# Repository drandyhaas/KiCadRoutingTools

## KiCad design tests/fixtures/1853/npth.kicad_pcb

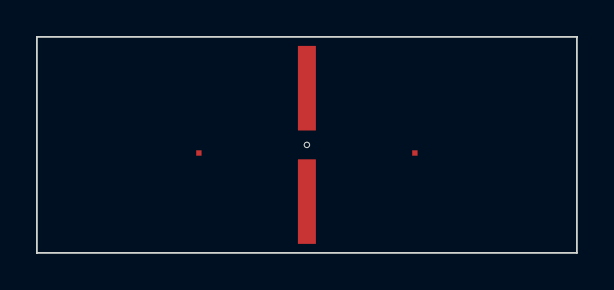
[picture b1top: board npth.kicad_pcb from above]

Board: 4 copper layers, 30.0 x 12.0 mm, 3 parts (0 on the bottom side), 2 nets, no tracks yet.

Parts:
H1: H1
P1: P1
W1: W1

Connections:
SIG: P1.1, P1.2
WALL: W1.1, W1.2

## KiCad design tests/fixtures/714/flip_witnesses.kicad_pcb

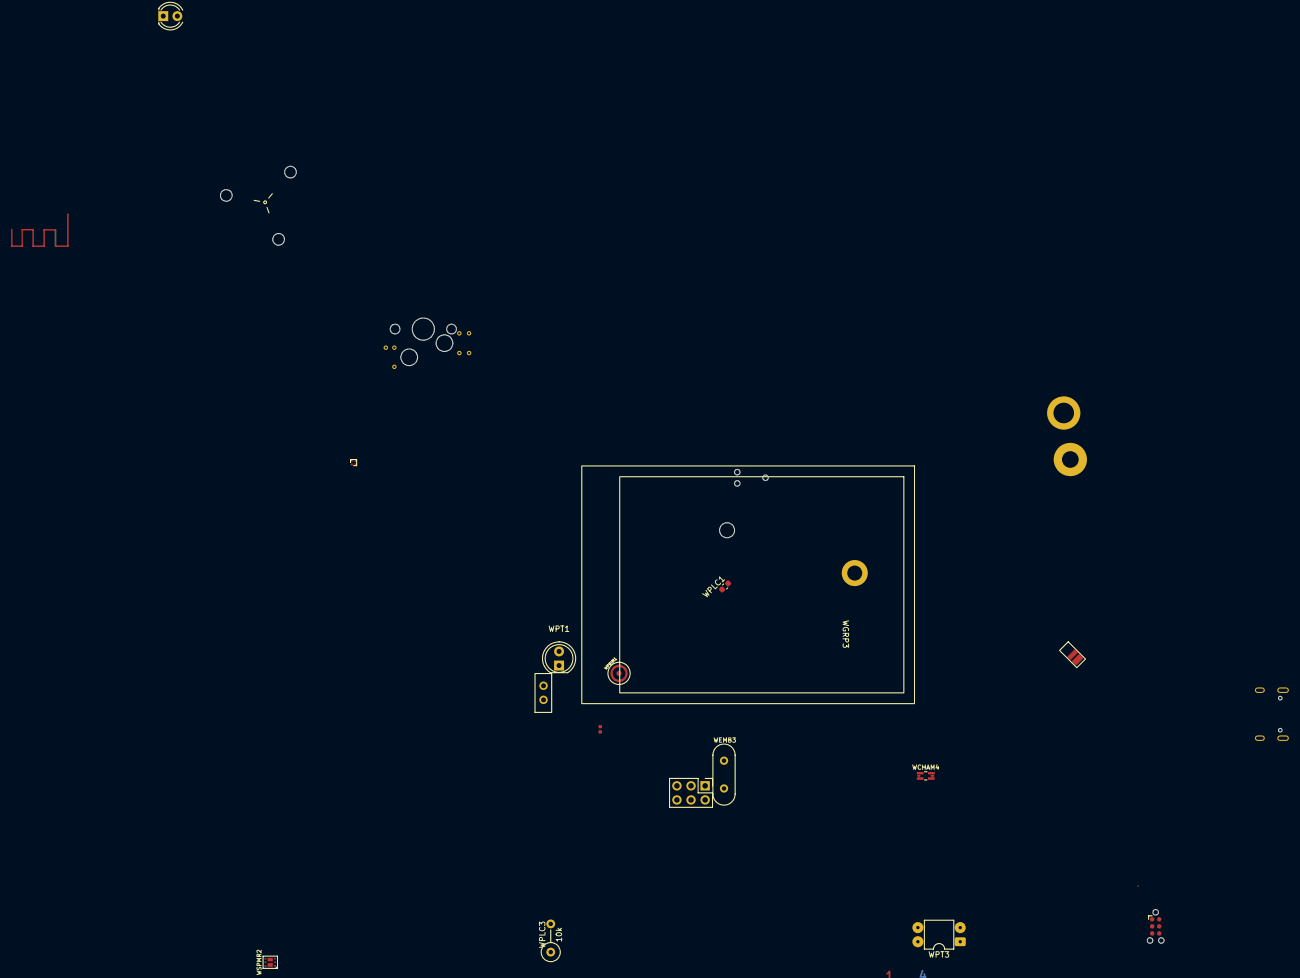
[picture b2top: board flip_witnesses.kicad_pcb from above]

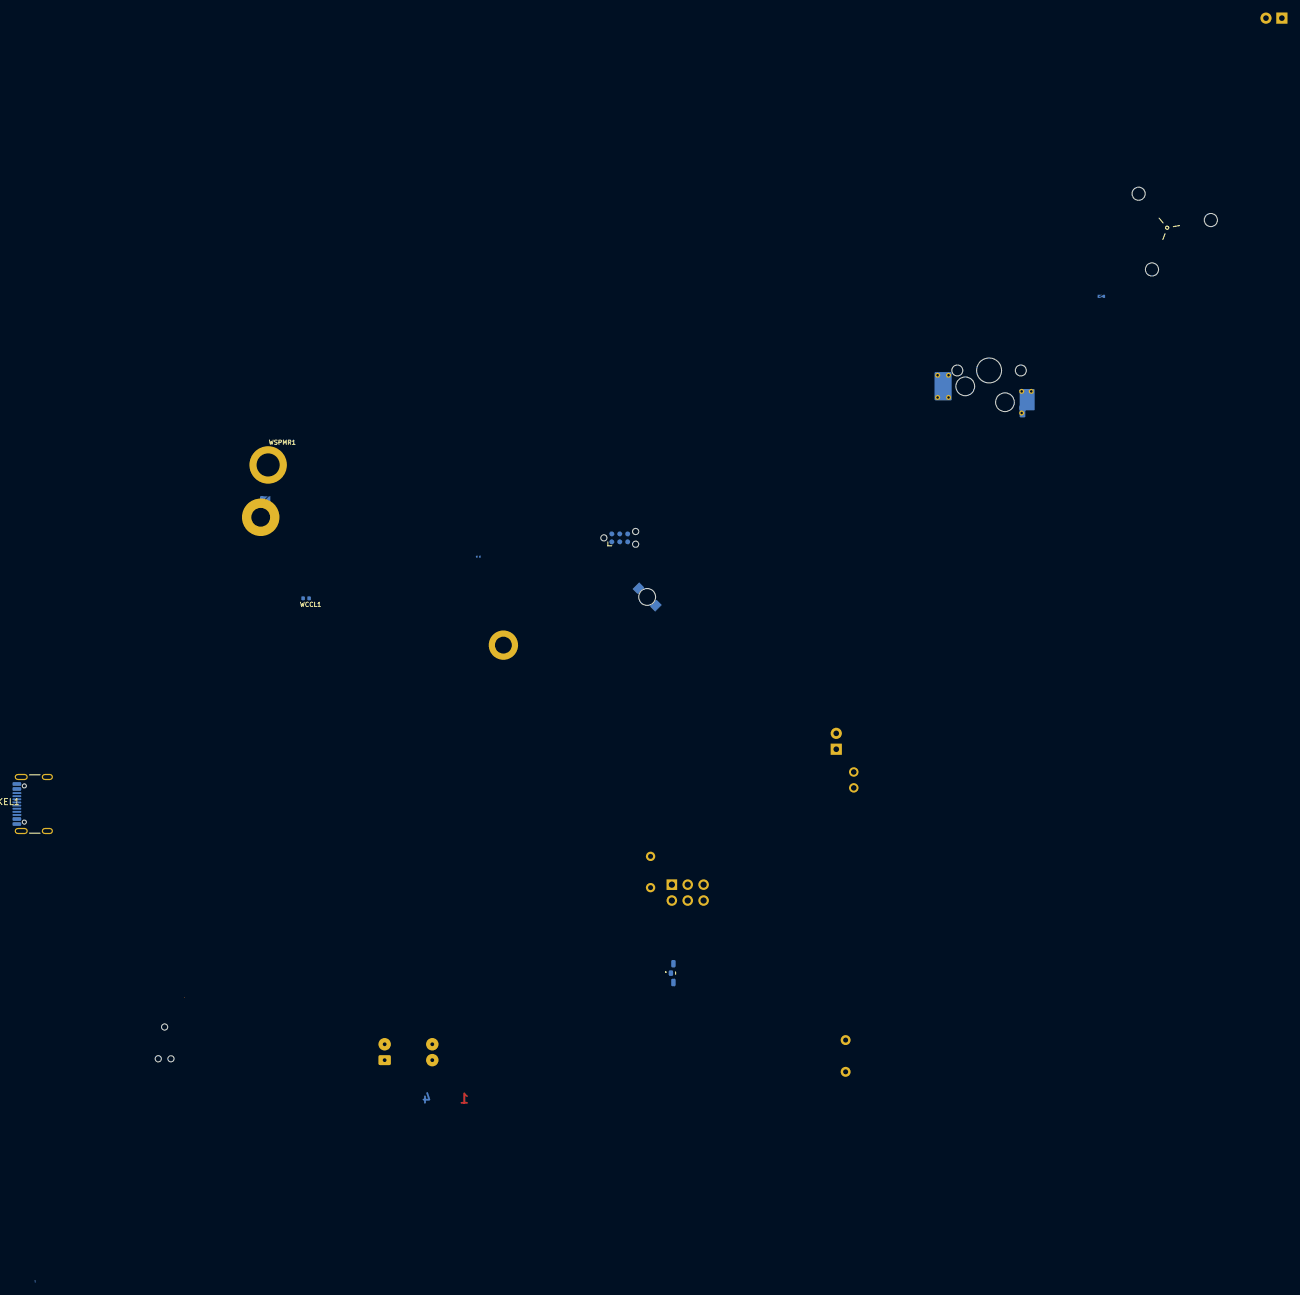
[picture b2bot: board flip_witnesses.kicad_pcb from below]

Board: 6 copper layers, 33 parts (11 on the bottom side), 6 nets, no tracks yet.

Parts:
WCCL1: R_49k9_0402; R_0402_1005Metric
WCCL2: R_0R01_330mW_0402; R_0402_1005Metric
WCHAM1: Net-Tie_2; NetTie-2_SMD_Pad0.127mm
WCHAM2: 100nF; C_0201
WCHAM3: Net-Tie_P0.127mm; NetTie-2_SMD_Pad0.127mm
WCHAM4: 5m; R_0805_2012Metric_4Kelvin
WEMB1: 2286211-3; TE_2286211-3
WEMB2: LED_Dual_KAK; 155124RG73200
WEMB3: 8 MHz; QUARTZ_TH
WGRP1: MountingHole; 90611A112_Screw_Mount_Nut
WGRP2: Battery_Connector
WGRP3: NHD-2.4-240320AF-CSXP
WKEL1: USB-C; USB_C_Receptacle_GCT_USB4105-xx-A_16P_TopMnt_Horizontal
WKEL2: AVR-ISP-6; PinHeader_2x03_P2.54mm_Vertical
WKEL3: MountingHole_Pad; MountingHole_2.7mm_M2.5_DIN965_Pad_reversible
WPLC1: 10nF; C_0603_1608Metric
WPLC2: HOLE; MountingHole_3mm
WPLC3: 10k; R_Axial_DIN0309_L9.0mm_D3.2mm_P5.08mm_Vertical
WPRIM1: Mic; B4013AM422-42
WPRIM2: PUDC_H; SolderJumper-2_1.2x0.5mm
WPRIM3: Jumper
WPRIM4: RED; LED_1206
WPRIM5: MX; MX-1U-Hotswap
WPRIM6: Antenna; 2.4GHz-meander-antenna-v2
WPT1: LED Red; LED_D5.0mm
WPT2: LED_Small_ALT; LED_D4.0mm
WPT3: PC817; DIP-4_W7.62mm
WSPMR1: Spacer_Drill3.7mm_H6mm_9774060151R
WSPMR2: SSM6N58NU; DFN_6_0.65MM_2x2MM_GDS
WSPMR3: 18-038BT
WZONE1: TC2030-IDC; Tag-Connect_TC2030-IDC-NL_2x03_P1.27mm_Vertical
WZONE2: Conn_02x03_Odd_Even; Tag-Connect_TC2030-IDC-NL_2x03_P1.27mm_Vertical
WZONE3: 4_Layer_Marker; 4_Layer_Markers

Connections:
+5V: WKEL2.2 (VCC), WPLC3.1
/USB_D+: WKEL1.A6 (D+), WKEL1.B6 (D+)
/USB_D-: WKEL1.A7 (D-), WKEL1.B7 (D-)
Earth: WKEL1.A1 (GND), WKEL1.A12 (GND), WKEL1.B1 (GND), WKEL1.B12 (GND), WKEL1.S1 (SHIELD), WPT3.3
GND: WCHAM1.2, WCHAM2.2, WCHAM3.2, WEMB1.1, WKEL2.6 (GND), WKEL3.1, WPLC1.1, WPLC2.1, WPRIM4.1 (K), WPT1.1 (K), WSPMR1.1, WZONE1.4, WZONE2.3, WZONE2.5
VBUS: WEMB2.2 (A), WKEL1.A4 (VBUS), WKEL1.A9 (VBUS), WKEL1.B4 (VBUS), WKEL1.B9 (VBUS)

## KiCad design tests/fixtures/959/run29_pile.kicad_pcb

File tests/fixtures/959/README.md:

# #959 fixtures: run 29's own declare-stage artifacts

Copied from the run-29 work directory (`wk/run29/esp_prog/` on branch `run29-harness`). `wk/` is gitignored, so the run itself is not in the repo, and these files are the minimum the #959 tests need to replay what that run saw.

| file | what it is | source file | sha256 (of the committed LF bytes) |
|---|---|---|---|
| `run29_pile.kicad_pcb` | the staged pile: every part at the board centre except the mechanical refs, with no locks | `board.kicad_pcb` | `c9ed55ee…828d` |
| `run29_pile.kicad_pro` | its project sibling (carries the DRC floor; never copy a board without it) | `board.kicad_pro` | `9a9ab694…6395` |
| `zone_plan_r1.json` | the run's first zone plan (six zoned blocks, `fiducial-nw` among them, `Ref[*]~2` in `must_lock`) | `zone_plan.json` | `702f8fc0…85b9` |
| `zone_plan_r2_lap5.json` | the lap-5 draft of the second plan, which the run amended within a minute. Reconstructed from the session record, not copied from a file: its two overlaps (1.60 and 0.6325 mm2) are the ones the lap-5 grade reported | (session record) | `81c101c8…2845` |

Readers: `run29_pile.kicad_pcb` (its `.kicad_pro` comes along as the sibling) is the pile in `test_959_decaps_auto`, `test_959_padless_blocks`, `test_959_pose_intent`, `test_959_rule_roster`, `test_1064_place_pose_same_net_stack`, `test_1100_1103_run37_followups`, `test_1178_decaps_from_shared_origin` and `test_check_assembly_pile_baseline`; `zone_plan_r1.json` is read by `test_959_rule_roster`, `zone_plan_r2_lap5.json` by `test_959_pose_intent`.

`asbuilt/` holds the design briefs of five as-built boards (esp_prog, glasgow_revC, splitflap_driver, tigard, ulx3s), written for #1000: the calibration set for how connector declarations compile to clauses (`docs/design-brief.md`, "Connector declarations compile to clauses"). No test reads them; they are the evidence that mapping was measured on.

The hashes are of the bytes git stores (LF line endings). A Windows checkout with `core.autocrlf` writes CRLF and hashes differently; pin against `git show HEAD:<path>`, not the working copy.

What the run's own record says about these files:

- The pile's decap census was measured ON THE PILE: `max_mm 0.0`, population 4, tethers 3, one cap (C1) beyond the radius. A strict `--declare-decaps` there derives a 0.0 limit.
- `zone_plan_r1.json` escapes the reference `Ref*` as `Ref[*]`, so run 29 never hit the fnmatch trap where `Ref*` also matches `Ref*~2`.
- The two `intent_zone_overlap` findings reported at lap 5 came from a later draft of the second plan, which the run amended within a minute. `zone_plan_r2_lap5.json` is that draft; both overlaps are satisfiable (WARNs since #959).

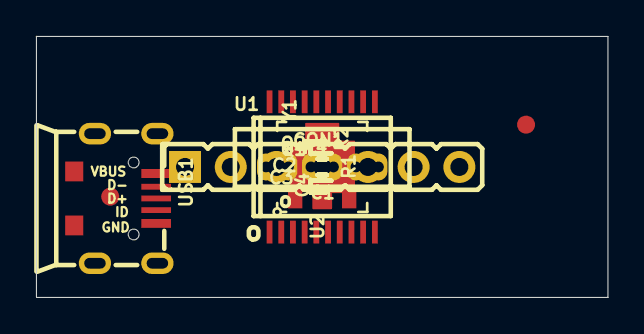
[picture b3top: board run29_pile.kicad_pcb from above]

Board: 2 copper layers, 31.8 x 14.5 mm, 18 parts (0 on the bottom side), 17 nets, no tracks yet.

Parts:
C1, C3: 2.2uF; C_0603_5MIL_DWS
C2, C4: 27pF; C_0402_5MIL_DWS
CON1: CON6; WU06SM
CON2: CON6; HN1x7
Q1, Q2: BC817-40(SOT23); SOT23
R1, R2: 1K; R_0402_5MIL_DWS
R3, R4: 100R; R_0402_5MIL_DWS
Ref*: Val**; Fiducial1x3_transp
Ref*#2: Val**; Fiducial1x3_transp
U1: CH340H/T; SSOP-20W
U2: ME6210-SOT89; SOT89
USB1: USB-uicro-B; USB-MICRO_MISB-SWMM-5B_LF
Y1: Q12MHz/20pF/10ppm/4P/3.2x2.5mm; TSX-3.2x2.5mm_GND(3)

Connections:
/+3.3V: C3.1, CON1.5, CON2.5, U1.5, U1.19, U2.3
/DCOM: CON1.2, CON2.2, Q1.3
/DTR: Q1.2, R2.2, U1.15
/D_N: U1.7, USB1.2
/D_P: U1.6, USB1.3
/EN: CON1.6, CON2.6, Q2.3
/RTS: Q2.2, R1.2, U1.16
/U0RXD: CON1.3, CON2.3, R3.1
/U0TXD: CON1.1, CON2.1, R4.1
GND: C1.2, C2.2, C3.2, C4.2, CON1.4, CON2.4, U1.8, U2.1, USB1.0, USB1.5, Y1.3
unnamed: C1.1, CON2.7, U2.2, USB1.1
unnamed: C2.1, U1.10, Y1.2
unnamed: C4.1, U1.9, Y1.1
unnamed: Q1.1, R1.1
unnamed: Q2.1, R2.1
unnamed: R3.2, U1.3
unnamed: R4.2, U1.4

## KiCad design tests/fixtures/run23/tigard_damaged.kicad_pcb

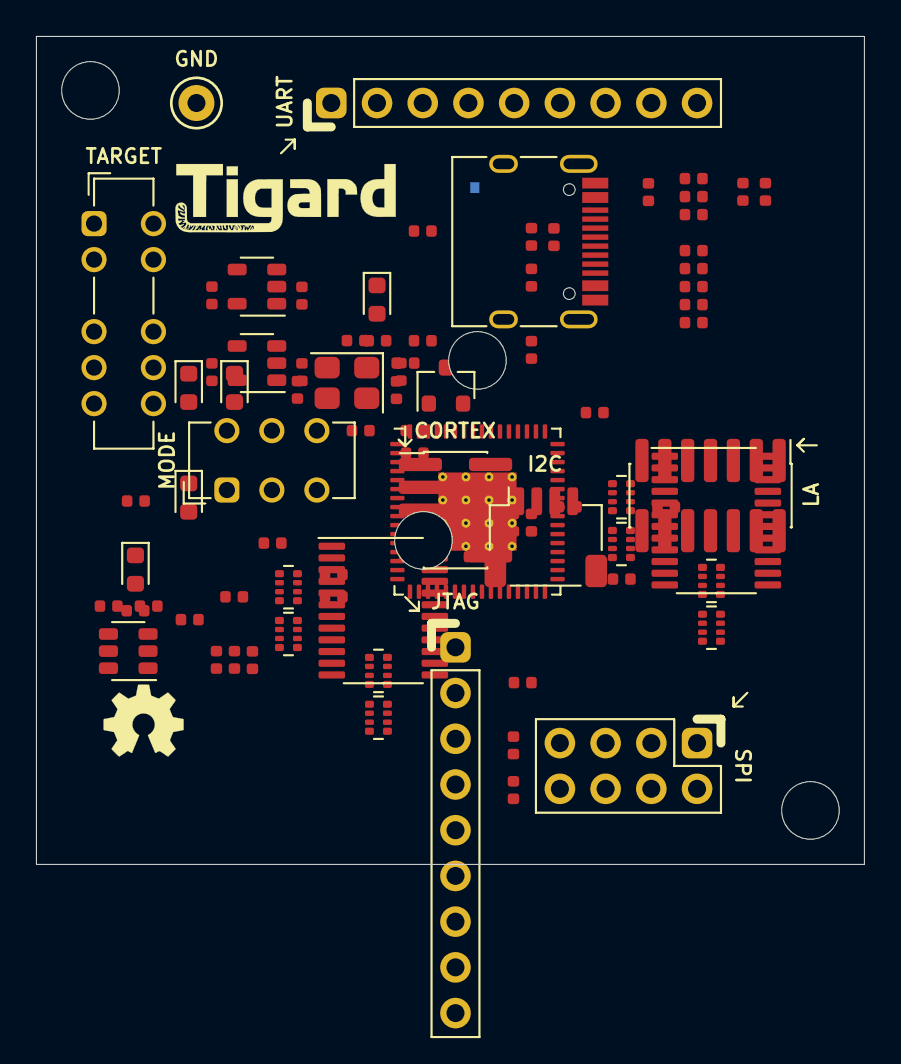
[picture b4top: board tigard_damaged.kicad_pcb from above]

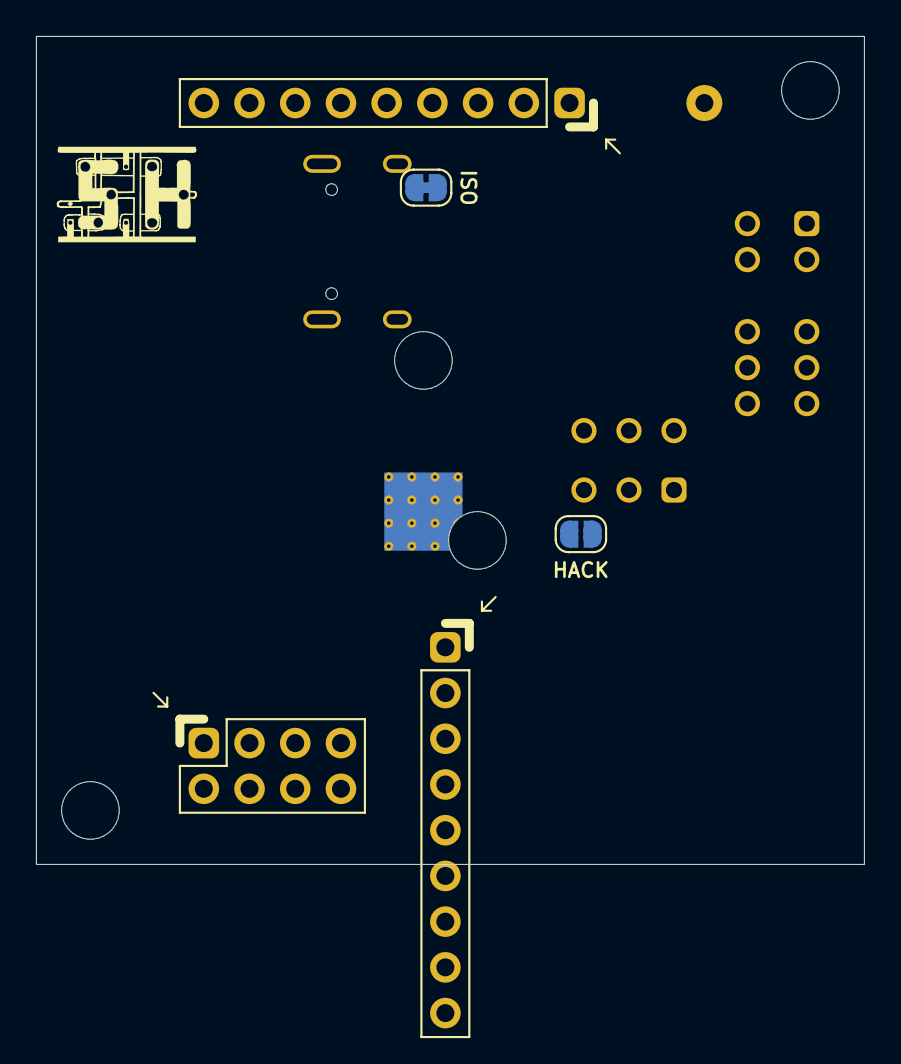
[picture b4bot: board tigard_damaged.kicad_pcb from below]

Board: 4 copper layers, 46.0 x 46.0 mm, 91 parts (3 on the bottom side), 85 nets, no tracks yet.

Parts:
C1, C2, C3, C4, C6, C7, C9, C10: 2u2; C_0402_1005Metric
C5, C8, C11, C12, C13, C14, C15, C16, C17, C18, C19, C20, C21, C22, C26: 100n; C_0402_1005Metric
C23, C24: 30pF; C_0402_1005Metric
C25: NF; C_0402_1005Metric
D1, D4: YELLOW; LED_0603_1608Metric
D2: BLUE; LED_0603_1608Metric
D3, D5: GREEN; LED_0603_1608Metric
FB1, FB2, FB3: 600R, 0.5A; L_0402_1005Metric
H1, H2, H3, H4: MountingHole; MountingHole_3.2mm_M3_ISO7380
J1: USB_C_Receptacle_USB2.0; USB_C_Receptacle_HRO_TYPE-C-31-M-12
J2: JTAG; PinHeader_1x09_P2.54mm_Vertical
J3: UART; PinHeader_1x09_P2.54mm_Vertical
J4: SPI; PinHeader_2x04_P2.54mm_Vertical
J5: CORTEX; PinHeader_2x05_P1.27mm_Vertical_SMD
J6: LA; PinHeader_2x07_P1.27mm_Vertical_SMD
J7: I2C; JST_SH_SM04B-SRSS-TB_1x04-1MP_P1.00mm_Horizontal
JP1: ISO; SolderJumper-2_P1.3mm_Bridged_RoundedPad1.0x1.5mm
JP2: HACK; SolderJumper-2_P1.3mm_Open_RoundedPad1.0x1.5mm
LOGO1: Logo_Open_Hardware_Small; OSHW-Symbol_4.4x4mm_SilkScreen
LOGO2: Logo_SH; Securing_Hardware_Logo
Q1: BSH103; SOT-23_RoundRect
R1, R2: 5k1; R_0402_1005Metric
R3, R17: 1M; R_0402_1005Metric
R4, R5, R8, R9, R11, R16: 330; R_0402_1005Metric
R6: 12k, 1%; R_0402_1005Metric
R7, R10, R12, R13, R14, R18, R19, R20, R21, R24: 10k; R_0402_1005Metric
R15: 2.2k; R_0402_1005Metric
R22: 2k2; R_0402_1005Metric
RN1, RN2, RN7, RN8: 100k; R_Array_Convex_4x0402_RoundRect
RN3, RN4, RN5, RN6: 100; R_Array_Convex_4x0402_RoundRect
SW1: TARGET; SW_ALPS_SSSS224100_DP4T
SW2: MODE; SW_CuK_JS202011CQN_DPDT_Straight
TP1: GND; TestPoint_Keystone_5000-5004_Miniature
U1: AP7365-18; SOT-23-5_RoundRect
U2: AP7365-33; SOT-23-5_RoundRect
U3: FT2232HQ; QFN-64-1EP_9x9mm_P0.5mm_EP4.35x4.35mm_ThermalVias
U4: 93LC46BT-I/OT; SOT-23-6_RoundRect
U5, U6: SN74LVC8T245; TSSOP-24_4.4x7.8mm_P0.65mm
Y1: 12MHz; Crystal_SMD_3225-4Pin_3.2x2.5mm_RoundRect

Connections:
+1V8: C2.1, SW1.9, U1.5
+3V3: C4.1, C14.1, C15.1, C16.1, C17.1, C18.1, C19.1, C20.1, FB1.1, FB2.1, R4.1, R5.1, R7.1, R8.2, R9.2, R10.1, R11.2, R12.1, R13.1, R14.1, R18.1, RN1.1, RN1.2, RN1.3, RN1.4, RN2.1, RN2.2, RN2.3, RN2.4, SW1.7, U2.5, U3.20, U3.31, U3.42, U3.50, U3.56, U4.6, U5.1, U6.1
+5V: C1.1, C3.1, C26.1, FB3.1, SW1.6, U1.1, U1.3, U2.1, U2.3
/AD0: RN2.5, U3.16, U5.10
/AD1: RN5.1, U3.17
/AD2: RN2.6, U3.18, U5.9
/AD3: RN5.2, U3.19
/AD4: RN2.7, U3.21, U5.8
/AD5: RN5.3, U3.22
/AD6: RN5.4, U3.23
/BD0: RN1.8, U3.38, U5.3
/BD1: RN1.7, U3.39, U5.4
/BD2: RN6.1, U3.40
/BD3: RN1.6, U3.41, U5.5
/BD4: RN1.5, U3.43, U5.6
/BD5: R22.1, RN2.8, U3.44, U5.7
/BD6: RN6.2, U3.45
/BD7: R22.2, U3.46
/CIPO: J2.5, J4.3, J5.6, SW2.4
/CLK: J2.3, J4.6, J5.4, J6.1, J7.4, RN3.8
/COPI: J2.4, J4.8, J5.8, J6.2, J7.3, JP2.1, R16.2, RN3.7
/CORTEX_PIN2: J5.2, SW2.2
/CS: J2.6, J4.1, J6.4, RN3.6, SW2.1
/DI: J6.3, RN8.1, SW2.5, U6.17
/EECLK: R14.2, U3.62, U4.4
/EECS: R12.2, U3.63, U4.5
/EEDATA: R15.1, U3.61, U4.3
/ICE_CDONE: J2.9, J3.4, J6.8, RN7.1, RN8.2, U6.16, U6.21
/RXLED: D3.1, U3.29
/SWDIO: JP2.2, R16.1, SW2.3, SW2.6
/TXLED: D4.1, U3.30
/UART_TX: J3.3, J6.7, RN4.5
/USB_DN: J1.A7, J1.B7, U3.7
/USB_DP: J1.A6, J1.B6, U3.8
/VBUS: FB3.2, J1.A4, J1.A9, J1.B4, J1.B9
/VPHY: C5.1, C6.1, FB1.2, U3.4
/VPLL: C7.1, C8.1, FB2.2, U3.9
/xPB4: J2.7, J6.5, RN3.5
/xPB5: J2.8, J5.10, J6.6, RN4.8
/~ENABLE: D5.1, R10.2, U3.60, U5.22, U6.22
/~UART_CTS: J3.6, RN7.2, U6.20
/~UART_DCD: J3.9, RN7.4, U6.18
/~UART_DSR: J3.8, RN7.3, U6.19
/~UART_DTR: J3.7, RN4.7
/~UART_RTS: J3.5, RN4.6
GND: C1.2, C2.2, C3.2, C4.2, C5.2, C6.2, C7.2, C8.2, C9.2, C10.2, C11.2, C12.2, C13.2, C14.2, C15.2, C16.2, C17.2, C18.2, C19.2, C20.2, C21.2, C22.2, C23.2, C24.2, C25.1, C26.2, D1.1, J1.A1, J1.A12, J1.B1, J1.B12, J2.2, J3.2, J4.7, J5.3, J5.5, J5.9, J6.9, J6.10, J7.1, J7.MP, Q1.2, R1.1, R2.2, R3.1, R6.1, R17.2, R19.2, R24.1, TP1.1, U1.2, U2.2, U3.1, U3.5, U3.10, U3.11, U3.13, U3.15, U3.25, U3.35, U3.47, U3.51, U3.65, U4.2, U5.11, U5.12, U5.13, U6.11, U6.12, U6.13, Y1.2, Y1.4
unnamed: C23.1, U3.2, Y1.1
unnamed: C24.1, U3.3, Y1.3
unnamed: C25.2, J1.S1, R3.2
unnamed: D1.2, R4.2
unnamed: D2.1, Q1.3
unnamed: D2.2, R5.2
unnamed: D3.2, R8.1
unnamed: D4.2, R9.1
unnamed: D5.2, R11.1
unnamed: J1.A5, R1.2
unnamed: J1.B5, R2.1
unnamed: J4.4, R21.2
unnamed: J4.5, R20.1
unnamed: R6.2, U3.6
unnamed: R7.2, U3.14
unnamed: R13.2, R15.2, U4.1
unnamed: R18.2, U5.2
unnamed: R19.1, U6.2
unnamed: RN3.1, U5.21
unnamed: RN3.2, U5.20
unnamed: RN3.3, U5.19
unnamed: RN3.4, U5.18
unnamed: RN4.1, U5.17
unnamed: RN4.2, U5.16
unnamed: RN4.3, U5.15
unnamed: RN4.4, U5.14
unnamed: RN5.5, U6.6
unnamed: RN5.6, U6.5
unnamed: RN5.7, U6.4
unnamed: RN5.8, U6.3
unnamed: RN6.5, U6.10
unnamed: RN6.6, U6.9
unnamed: RN6.7, U6.8
unnamed: RN6.8, U6.7
unnamed: RN8.3, U6.15
unnamed: RN8.4, U6.14
VREF: C21.1, C22.1, JP1.2, Q1.1, R17.1, R24.2, RN7.5, RN7.6, RN7.7, RN7.8, RN8.5, RN8.6, RN8.7, RN8.8, SW1.8, U5.23, U5.24, U6.23, U6.24
VREG: C9.1, C10.1, C11.1, C12.1, C13.1, U3.12, U3.37, U3.49, U3.64
VTARGET: J2.1, J3.1, J4.2, J5.1, J7.2, JP1.1, R20.2, R21.1, SW1.10

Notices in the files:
tests/fixtures/714/flip_witnesses.kicad_pcb:
Licensed under CERN OHL v.1.2
tests/fixtures/run23/tigard_damaged.kicad_pcb:
Copyright Franklin Harding 2020
Licensed under CC-BY-SA 4.0
parts and their libraries:
License: Apache-2.0
